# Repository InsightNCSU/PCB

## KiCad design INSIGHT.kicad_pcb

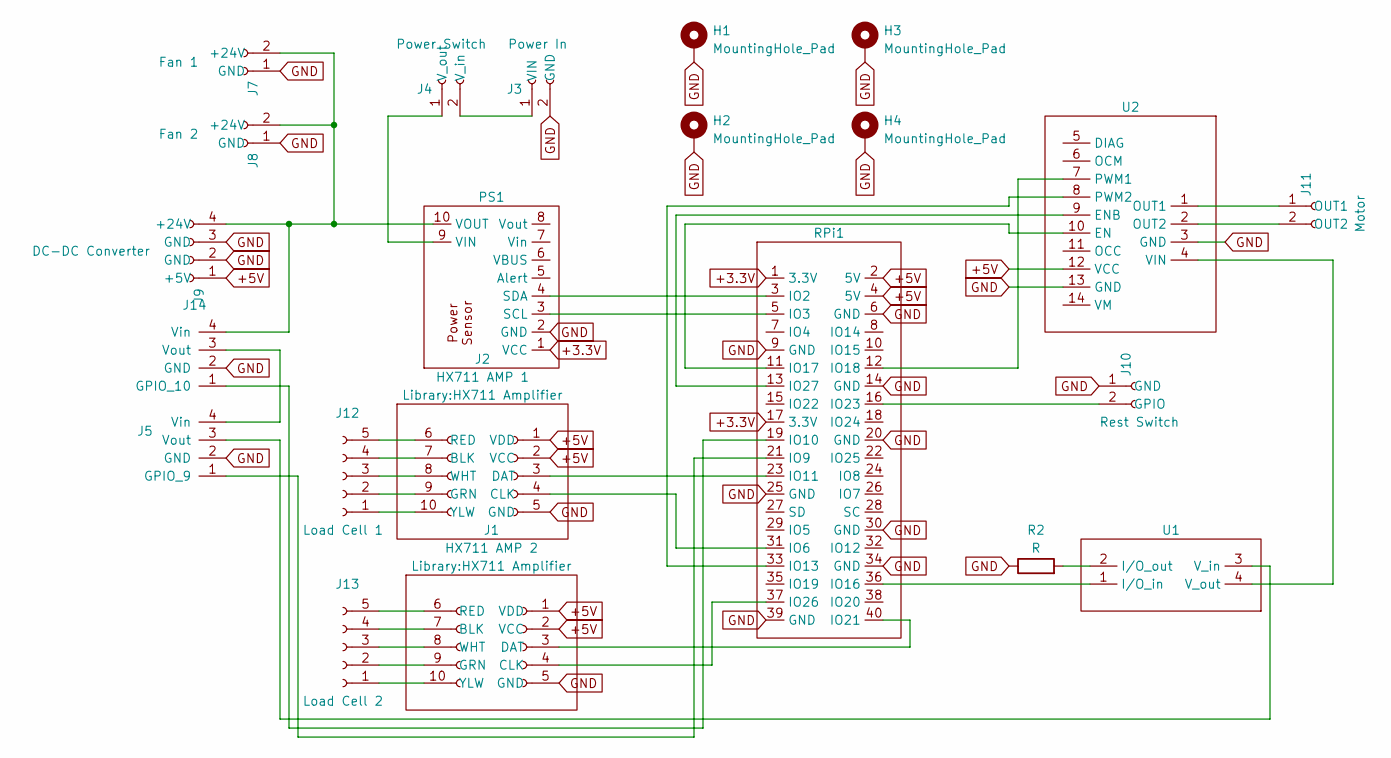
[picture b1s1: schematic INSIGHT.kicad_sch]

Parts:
H1, H2, H3, H4: MountingHole_Pad; MountingHole_3.2mm_M3_Pad
J1: HX711 AMP 2; HX711 Amplifier
J2: HX711 AMP 1; HX711 Amplifier
J3: Power In; PinSocket_1x02_P2.54mm_Vertical
J4: Power Switch; PinSocket_1x02_P2.54mm_Vertical
J5: E-Stop 2; PinSocket_1x04_P2.54mm_Vertical
J7: Fan 1; PinSocket_1x02_P2.54mm_Vertical
J8: Fan 2; PinSocket_1x02_P2.54mm_Vertical
J9: DC-DC Converter; PinSocket_1x04_P2.54mm_Vertical
J10: Rest Switch; PinSocket_1x02_P2.54mm_Vertical
J11: Motor; PinSocket_1x02_P2.54mm_Vertical
J12: Load Cell 1; PinSocket_1x05_P2.54mm_Vertical
J13: Load Cell 2; PinSocket_1x05_P2.54mm_Vertical
J14: E-Stop 1; PinSocket_1x04_P2.54mm_Vertical
PS1: Power Sensor
R2: R; R_Axial_DIN0207_L6.3mm_D2.5mm_P10.16mm_Horizontal
RPi1: PinSocket_2x20_P2.54mm_Vertical
U1: MOSFET Relay
U2: Motor_Driver

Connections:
+3.3V: PS1.1 (VCC), RPi1.1 (3.3V), RPi1.17 (3.3V)
+5V: J1.1 (VDD), J1.2 (VCC), J2.1 (VDD), J2.2 (VCC), J9.1 (+5V), RPi1.2 (5V), RPi1.4 (5V), U2.12 (VCC)
GND: H1.1, H2.1, H3.1, H4.1, J1.5 (GND), J2.5 (GND), J3.2 (GND), J5.2 (GND), J7.1 (GND), J8.1 (GND), J9.2 (GND), J9.3 (GND), J10.1 (GND), J14.2 (GND), PS1.2 (GND), R2.1, RPi1.6 (GND), RPi1.9 (GND), RPi1.14 (GND), RPi1.20 (GND), RPi1.25 (GND), RPi1.30 (GND), RPi1.34 (GND), RPi1.39 (GND), U2.3 (GND), U2.13 (GND); also elsewhere on the board
unnamed: J1.7 (BLK), J13.4
unnamed: J1.4 (CLK), RPi1.37 (IO26)
unnamed: J1.3 (DAT), RPi1.40 (IO21)
unnamed: J1.9 (GRN), J13.2
unnamed: J1.6 (RED), J13.5
unnamed: J1.8 (WHT), J13.3
unnamed: J1.10 (YLW), J13.1
unnamed: J2.4 (CLK), RPi1.31 (IO6)
unnamed: J2.3 (DAT), RPi1.23 (IO11)
unnamed: J3.1 (VIN), J4.2 (V_in)
unnamed: J4.1 (V_out), PS1.9 (VIN)
unnamed: J5.1 (GPIO_9), RPi1.21 (IO9)
unnamed: J5.3 (Vout), U1.3 (V_in)
unnamed: J10.2 (GPIO), RPi1.16 (IO23)
unnamed: J11.1 (OUT1), U2.1 (OUT1)
unnamed: J11.2 (OUT2), U2.2 (OUT2)
unnamed: J2.10 (YLW), J12.1
unnamed: J2.9 (GRN), J12.2
unnamed: J2.8 (WHT), J12.3
unnamed: J2.7 (BLK), J12.4
unnamed: J2.6 (RED), J12.5
unnamed: J14.1 (GPIO_10), RPi1.19 (IO10)
unnamed: J7.2 (+24V), J8.2 (+24V), J9.4 (+24V), J14.4 (Vin), PS1.10 (VOUT)
unnamed: J5.4 (Vin), J14.3 (Vout)
unnamed: PS1.3 (SCL), RPi1.5 (IO3)
unnamed: PS1.4 (SDA), RPi1.3 (IO2)
unnamed: RPi1.33 (IO13), U2.8 (PWM2)
unnamed: RPi1.36 (IO16), U1.1 (I/O_in)
unnamed: RPi1.11 (IO17), U2.10 (EN)
unnamed: RPi1.12 (IO18), U2.7 (PWM1)
unnamed: RPi1.13 (IO27), U2.9 (ENB)
unnamed 34: R2.2, U1.2 (I/O_out); also elsewhere on the board
unnamed: U1.4 (V_out), U2.4 (VIN)

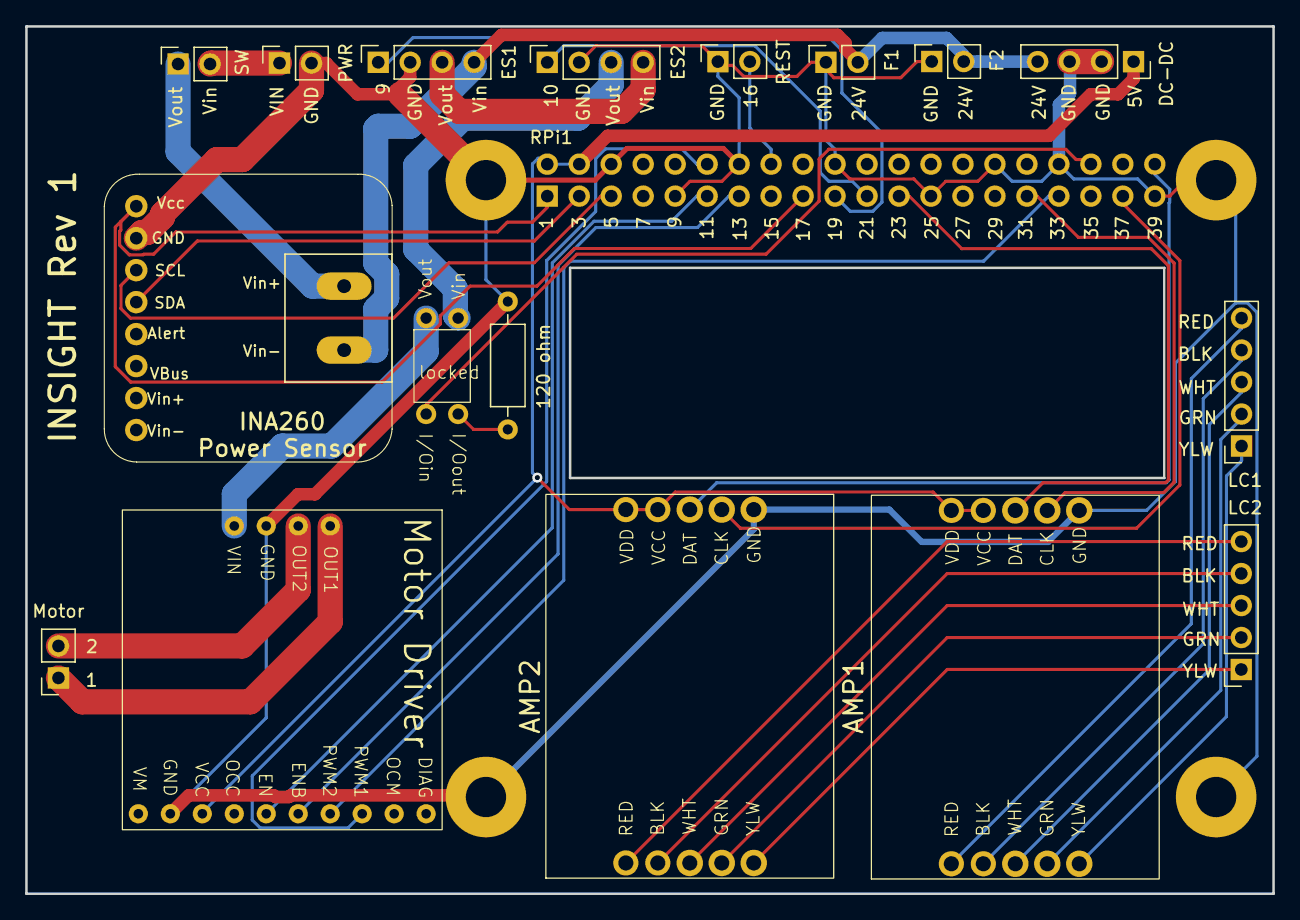
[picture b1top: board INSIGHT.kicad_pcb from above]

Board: 2 copper layers, 99.1 x 68.9 mm, 22 parts (1 on the bottom side), 36 nets.

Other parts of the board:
120 ohm: R; R_Axial_DIN0207_L6.3mm_D2.5mm_P10.16mm_Horizontal

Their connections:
GND: 120 ohm.1; also elsewhere on the board
unnamed 34: 120 ohm.2; also elsewhere on the board

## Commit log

2025-05-09 Rename KicadPCB.pdf to Media/KicadPCB.pdf
2025-05-09 Rename Screenshot 2025-05-08 211317.png to Media/PCB.png
2025-05-09 Rename KicadSchematic.pdf to Media/KicadSchematic.pdf
2025-08-08 Adding proj
2025-08-08 New schematic
